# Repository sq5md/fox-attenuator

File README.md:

# Tłumik odbiorczy do łowów na lisa 
Przedmiotem opisu jest urządzenie do tłumienia sygnału pochodzącego z anteny w celu umożliwienia kierunkowego namierzania bliskich urządzeń nadawczych małej mocy takich jak np. nadajniki do łowów na lisa.

Projekt powstał jako potrzeba klubowa SP5YAM z Komorowa.

Autorzy:

Elektronika + oprogramowanie: **Marcin SQ5MD**

Obudowa: **Michał SP5LEL**

Konsultacje: **Klub SP5YAM**

## Zanim zbudujesz

Zanim zbudujesz, miej na uwadze że PCB v1 zawiera błędy i wymaga **cięcia ścieżek**, dolutowania 3 elementów oraz **poprowadzenia 2 cienkich kynarów do układu QFN**.

Projekt PCB v2 w toku.

## Opis głównych funkcji:

- 2 złącza SMA, jedno do podłączenia anteny, drugie do podłączenia odbiornika.
- Zasilanie z 1 ogniwa 18650
- Wbudowana ładowarka 500mA (USB C)
- Sygnalizacja naładowania na diodzie RGB
- Sygnalizacja tłumienia na diodzie RGB oraz na pasku 5xLED
- Interfejs użytkownika - enkoder kwadraturowy (12 imp na obrót) z przyciskiem
- Tłumienie teoretyczne 0-63dB z krokiem co 0,5dB
- Bypass antenowy 50Ω - do namierzania bez kierunku z bardzo bliskiej odległości
- Tłumienie zmierzone: 2.2-64.2dB (bypass do 80dB)
- Auto Power Off po określonym czasie nieaktywności
- Dioda RGB

## Obsługa

Urządzenie po włączeniu jest od razu gotowe do pracy sygnalizując to zaświeceniem diody LED na zielono.
Kręcenie enkoderem powoduje odpowiednio zwiększenie lub zmniejszenie tłumienia z krokiem 0.5dB. 

Stan tłumienia sygnalizowany jest diodą RGB:
- Intensywny zielony - brak tłumienia
- Zielony-poprzez żółty, pomarańczowy, czerwony - aktywne tłumienie w zależności od koloru LED
- Intensywny czerwony - tłumienie maksymalne
- Niebieski - stan odcięcia anteny. Bypass Z=50Ω.

Urządzenie włączamy i wyłączamy przyciskiem na enkoderze.

Urządzenie posiada wbudowaną ładowarkę (MCP73831), a stan naładowania sygnalizowany jest kolorem fioletowym.

Projekt można przetestować na stoisku SP5YAM w Burzeninie 2026 podczas zabawy w łowy na lisa. Dostępne są 2 sztuki.

## Konstrukcja

Tor antenowy układu składa się z poszczególnych elementów (kolejność od strony podłączania odbiornika):
- Złącze SMA (żeńskie)
- RF-Switch AS179 (rozdziela tor odbiorczy na tor antenowy i bypass Z=50Ω)
	- Do anteny: 2 x cyfrowy tłumik regulowany Berex BDA4601 sterowany z mikrokontrolera
	- Bypass: Rezystancja Z=50Ω, pomija oba tłumiki.

 Układ sterowany jest z mikrokontrolera RP2040 (płyta RP2040-Zero od Waveshare https://www.waveshare.com/wiki/RP2040-Zero )

Interfejs użytkownika stanowi enkoder kwadraturowy z przyciskiem, 5 diod LED, dioda LED RGB.

Urządzenie jest zasilane z jednego ogniwa Li-Ion 18650, oraz posiada wbudowaną ładowarkę MCP73831.

Elementy Q1 i D5 pozwalają zrealizować funkcję programowego wyłączenia urządzenia..

### Schemat

### PCB

Płytka drukowana wykonana została w technologii 2 warstwowej na laminacie FR4 o grubości 0.6mm aby zapewnić najlepsze dopasowanie do impedancji 50Ω.

### Oprogramowanie

#### Moduły

Oprogramowanie układu oparte jest o projekt Zephyr, co przyspieszyło stworzenie projektu. Modułowa konstrukcja oprogramowania pozawala utrzymać porządek i lepiej zrozumieć budowę układu. W układzie można wydzielić kilka głównych modułów które komunikują się ze sobą za pomocą wiadomości wysyłanych przez magistralę EventBus.  
Magistrala EventBus pozwala każdemu z modułów na subskrypcję poszczególnych rodzajów eventów (model Publish/Subscribe).

##### Moduł InputListener

Moduł odpowiada za odpowiedni odczyt eventów z systemu Zephyr i ich wysłanie na magistralę eventów EventBus.
Eventy które wysyła to:
- EncoderRotated(lewo/prawo) - (gdy wykryto przekręcenie enkodera w lewo lub prawo)
- EncoderPressEvent(wciśnięcie/puszczenie) - gdy wyrkryto wciśnięcie lub puszczenie przycisku
- ChargerEvent - gdy wykryto stan naładowania z ładowarki
##### Moduł logiki aplikacji

Obsługuje wiadomości:
- EncoderRotated - wysłanie eventu AttenuatorChange
- EncoderPressEvent - wysłanie eventu PowerOff
- ChargerEvent - wysłanie eventu RgbLedSet()
- AttenuationInfo - wysłanie eventu RgbLedSet oraz LedMatrixSet w zależności od wartości tłumienia

##### Moduł HW
Obsługuje wiadomości:
- LedMatrixSet - ustawienie stanu na diodach 5xLED
- PowerOff - wyłączenie układu
- RgbLedSet - ustawienie odpowiedniego koloru na diodzie RGB
- ApplyAttenuatorChange - zmiana tłumienia (lub bypass)

#### Bootloader
Mikrokontroler posiada wbudowany bootloader.
Aktualizacja oprogramowania jest możliwa za pomocą przewodu USB-C.
Jest to standardowy bootloader wbudowany w mikrokontroler RP2040.

### Obudowa

Do układu powstała obudowa wykonana w technologii druku 3D FDM, autorem obudowy jest Michał SP5LEL.
Na moment pisania tej treści nie ma dostępnych fotografii obudowy.

### Fotografie

## Pomiary

Urządzenie pomiarowe:
NanoVNA V2 od NanoRFE (https://nanorfe.com/pl/)
Aplikacja:
VNA_View na Linux

Parametry pomiarowe:
Sweep 144-440MHz, 1024 punkty, AVG=5
kalibracja SOLT

### Minimalne tłumienie

### Połowa skali

### Maksymalne tłumienie

### Bypass

Tor bypassu jest najbardziej wrażliwy na ekranowanie urządzenia.

## TODO:

- [ ] Poprawki PCB: brak sygnału LE, brak DC-blockerów RF
- [ ] Diody LED THT zamiast SMD
- [ ] Tylko jeden tłumik regulowany, drugi stały 30dB
- [ ] Wymiana ładowarki jest bardzo trudna - montować układ inaczej
- [ ] Integracja z odbiornikiem (żeby nie trzeba było podłączać zewnętrznego odbiornika)
- [ ] Dodać pomiar napięcia baterii
- [ ] Wrzucić do releases plik uf2

## Przeróbka PCB v1 aby działała

## Edytor schematów i pcb

Stworzone w Kicad 10.0.4

## Jak skompilować

1. Zainstaluj Zephyra: https://docs.zephyrproject.org/latest/develop/getting_started/index.html
2. Zainstaluj i skonfiguruj CLion: https://docs.zephyrproject.org/latest/develop/tools/clion.html
3. Otwórz projekt in CLion, otwórz folder w którym znajduje się główny plik CMakeLists.txt (w momencie pisania tej treści jest to folder 'software/fox-attenuator')
4. Uruchom płytkę RP2040-Zero w trybie bootloadera a następnie wybierz target "flash" w CLion i uruchom budowanie projektu.

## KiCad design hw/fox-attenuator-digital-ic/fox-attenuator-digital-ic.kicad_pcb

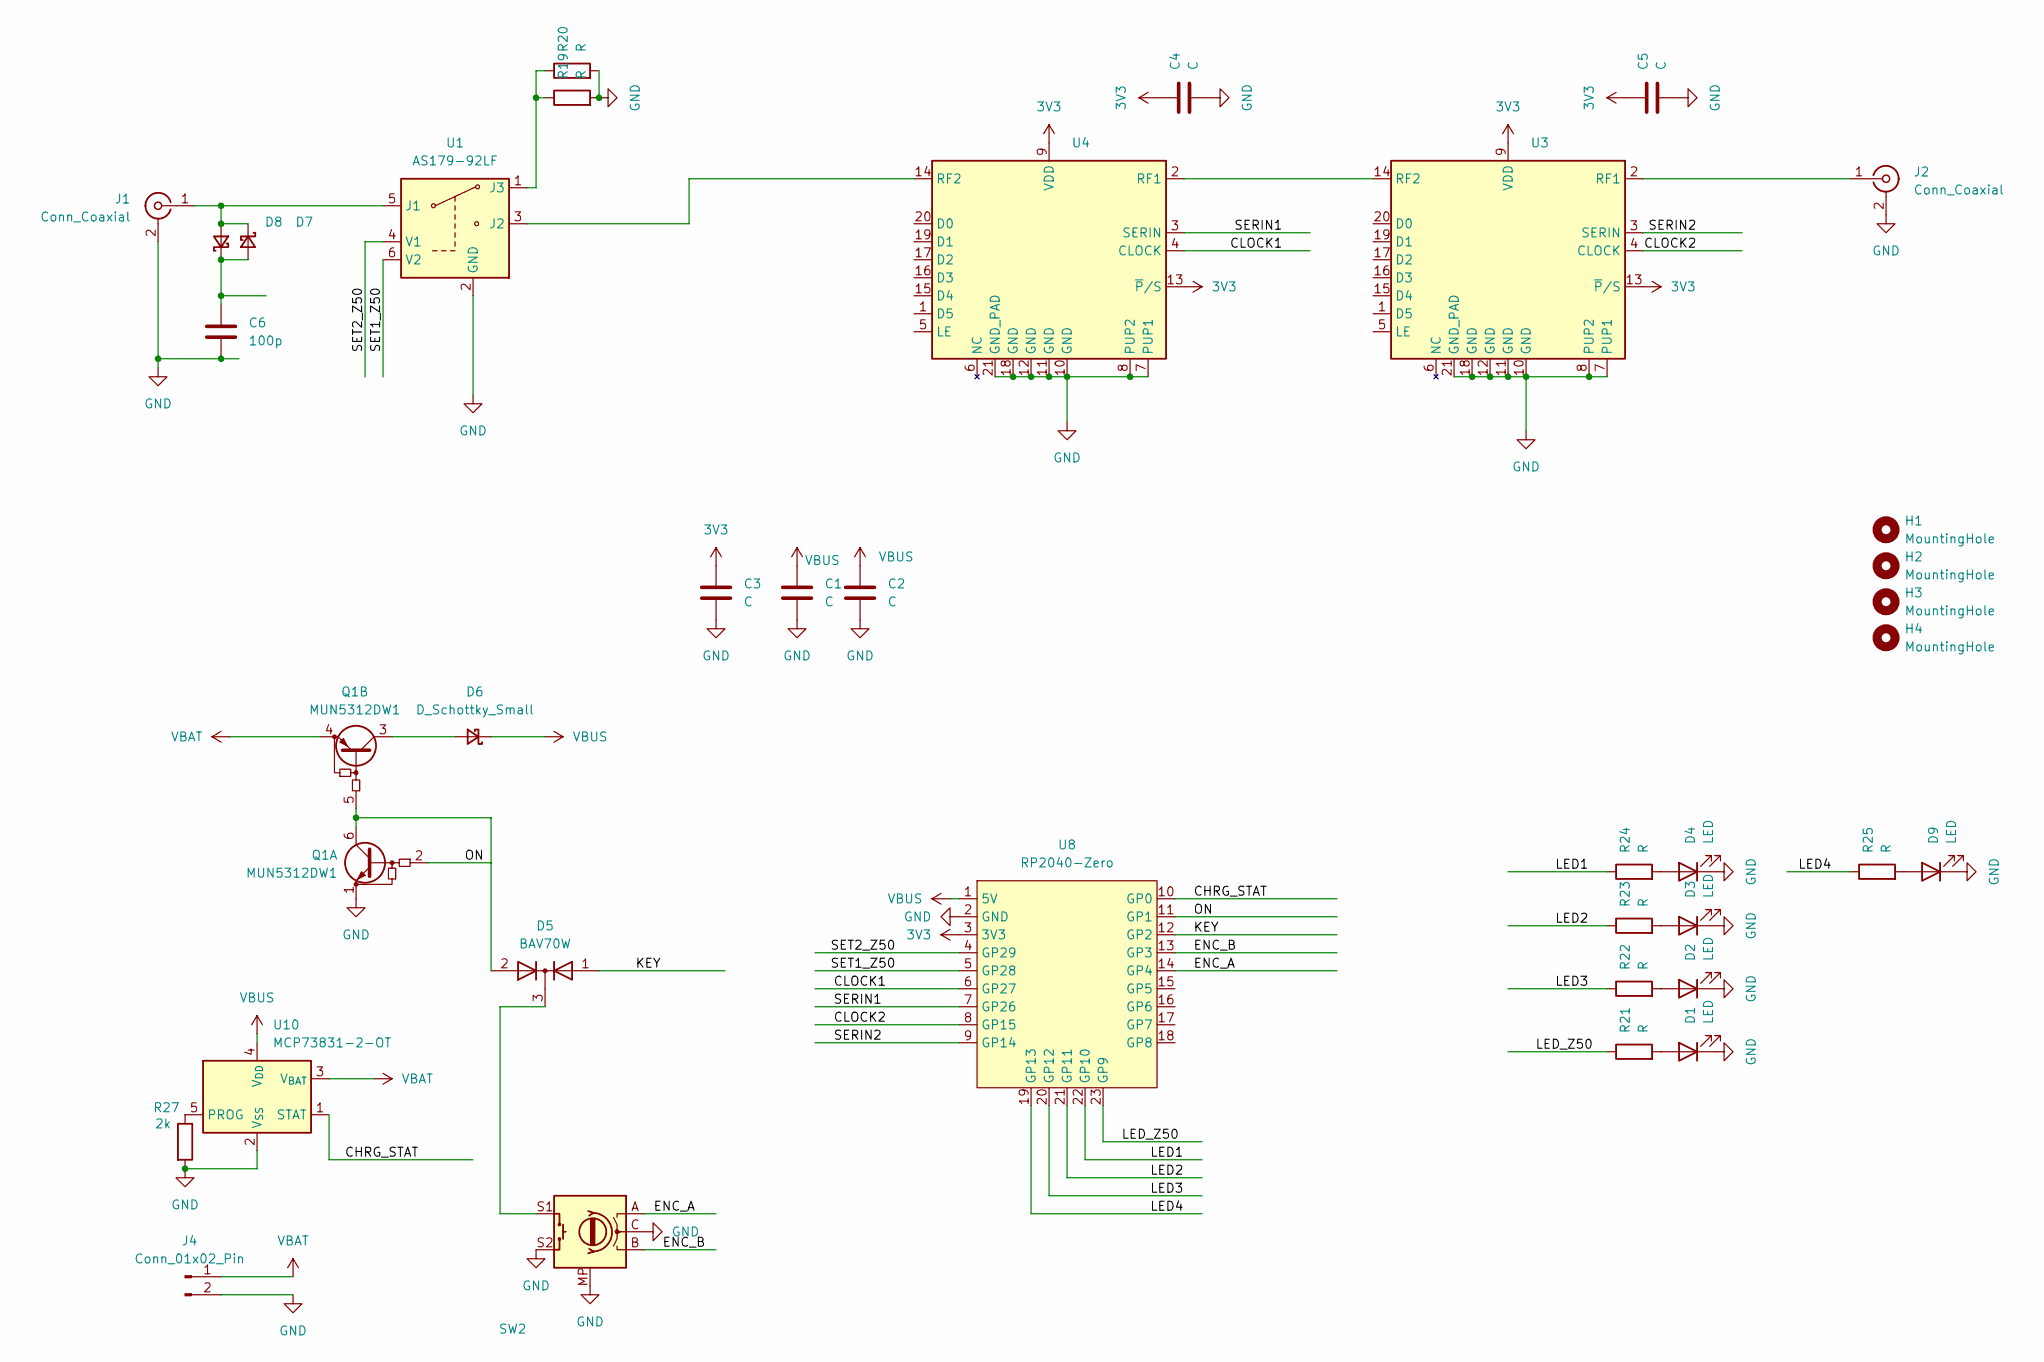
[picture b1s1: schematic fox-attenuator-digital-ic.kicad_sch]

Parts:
C1, C2, C3, C4, C5: C; C_0805_2012Metric_Pad1.18x1.45mm_HandSolder
C6: 100p; C_0805_2012Metric_Pad1.18x1.45mm_HandSolder
D1, D2, D3, D4, D9: LED; LED_0603_1608Metric_Pad1.05x0.95mm_HandSolder
D5: BAV70W; SOT-323_SC-70
D6, D7, D8: D_Schottky_Small; D_0603_1608Metric
H1, H2, H3, H4: MountingHole; MountingHole_3.2mm_M3_Pad_TopBottom
J1, J2: Conn_Coaxial; SMA_Molex_73251-1153_EdgeMount_Horizontal
J4: Conn_01x02_Pin; JST_PH_B2B-PH-K_1x02_P2.00mm_Vertical
Q1: MUN5312DW1; SOT-363_SC-70-6
R19, R20, R21, R22, R23, R24, R25: R; R_0603_1608Metric_Pad0.98x0.95mm_HandSolder
R27: 2k; R_0603_1608Metric
SW2: RotaryEncoder_Switch_MP; RotaryEncoder_Alps_EC11E-Switch_Vertical_H20mm
U1: AS179-92LF; SOT-363_SC-70-6
U3, U4: TQFN-20-1EP_4x4mm_P0.5mm_EP2.1x2.1mm
U8: RP2040-Zero; RP2040 Zero
U10: MCP73831-2-OT; SOT-23-5

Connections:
3V3: C3.1, C4.1, C5.1, U3.9 (VDD), U3.13 (~P/S), U4.9 (VDD), U4.13 (~P/S), U8.3 (3V3)
/CHRG_STAT: U8.10 (GP0), U10.1 (STAT)
/CLOCK1: U4.4 (CLOCK), U8.6 (GP27)
/CLOCK2: U3.4 (CLOCK), U8.8 (GP15)
/ENC_A: SW2.A, U8.14 (GP4)
/ENC_B: SW2.B, U8.13 (GP3)
/KEY: D5.1 (A), U8.12 (GP2)
/LED1: R24.1, U8.22 (GP10)
/LED2: R23.1, U8.21 (GP11)
/LED3: R22.1, U8.20 (GP12)
/LED4: R25.1, U8.19 (GP13)
/LED_Z50: R21.1, U8.23 (GP9)
/ON: Q1.2 (B1), U8.11 (GP1)
/SERIN1: U4.3 (SERIN), U8.7 (GP26)
/SERIN2: U3.3 (SERIN), U8.9 (GP14)
/SET1_Z50: U1.6 (V2), U8.5 (GP28)
/SET2_Z50: U1.4 (V1), U8.4 (GP29)
GND: C1.2, C2.2, C3.2, C4.2, C5.2, C6.2, D1.1 (K), D2.1 (K), D3.1 (K), D4.1 (K), D9.1 (K), H3.1, J1.2 (Ext), J2.2 (Ext), J4.2, Q1.1 (E1), R19.2, R20.2, R27.2, SW2.C, SW2.MP, SW2.S2, U1.2 (GND), U3.7 (PUP1), U3.8 (PUP2), U3.10 (GND), U3.11 (GND), U3.12 (GND), U3.18 (GND), U3.21 (GND_PAD), U4.7 (PUP1), U4.8 (PUP2), U4.10 (GND), U4.11 (GND), U4.12 (GND), U4.18 (GND), U4.21 (GND_PAD), U8.2 (GND), U10.2 (V_{SS})
unnamed: D1.2 (A), R21.2
unnamed: D2.2 (A), R22.2
unnamed: D3.2 (A), R23.2
unnamed: D4.2 (A), R24.2
unnamed: D5.3 (K), SW2.S1
unnamed: D6.2 (A), Q1.3 (C2)
unnamed: C6.1, D7.2 (A), D8.1 (K)
unnamed: D7.1 (K), D8.2 (A), J1.1 (In), U1.5 (J1)
unnamed: D9.2 (A), R25.2
unnamed: J2.1 (In), U3.2 (RF1)
unnamed: D5.2 (A), Q1.5 (B2), Q1.6 (C1)
unnamed: U1.3 (J2), U4.14 (RF2)
unnamed: R19.1, R20.1, U1.1 (J3)
unnamed: U3.14 (RF2), U4.2 (RF1)
unnamed: R27.1, U10.5 (PROG)
VBAT: J4.1, Q1.4 (E2), U10.3 (V_{BAT})
VBUS: C1.1, C2.1, D6.1 (K), U8.1 (5V), U10.4 (V_{DD})

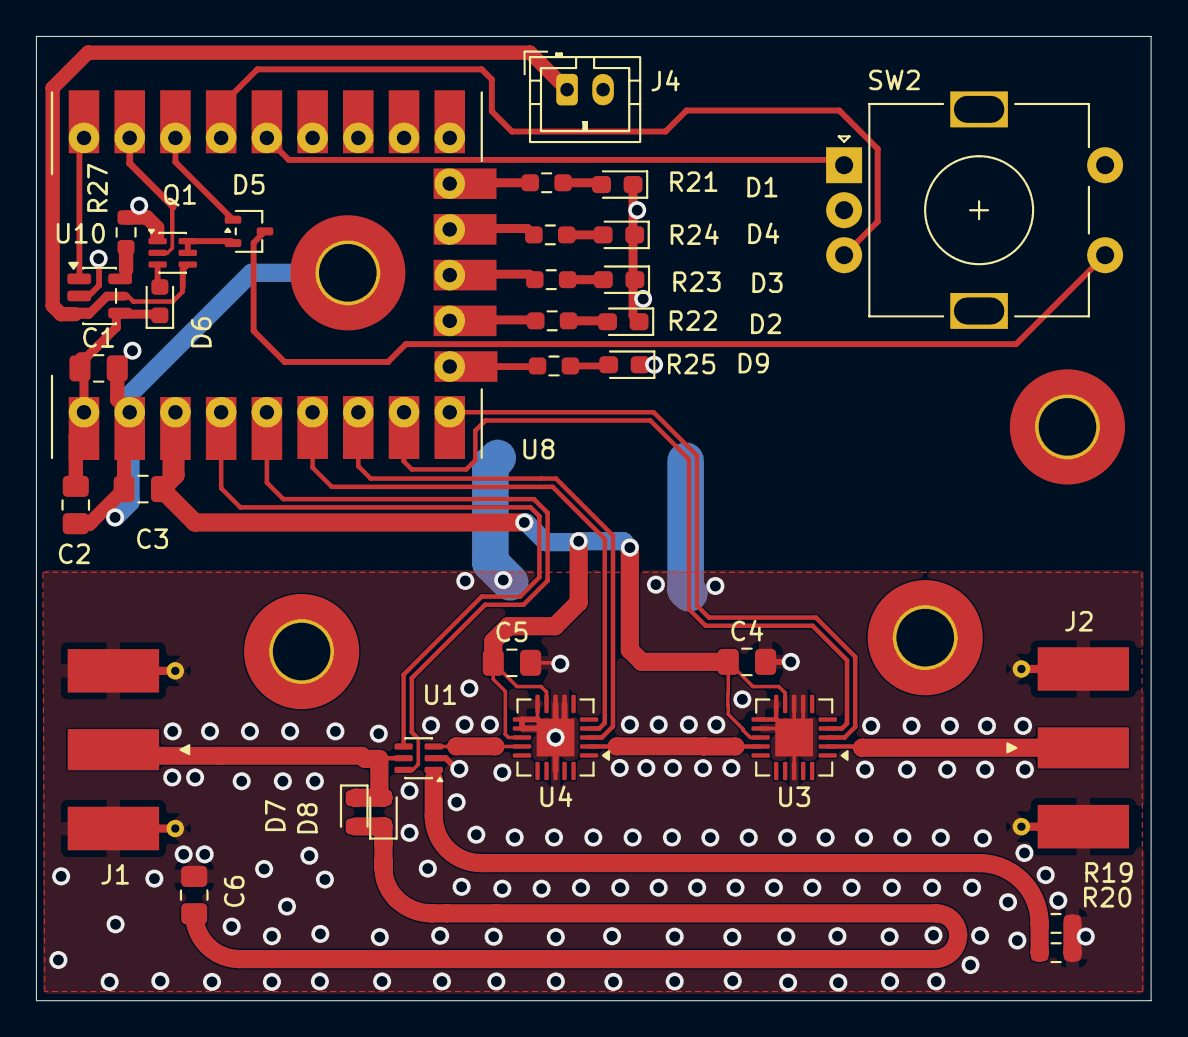
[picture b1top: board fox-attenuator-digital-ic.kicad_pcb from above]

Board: 2 copper layers, 61.9 x 53.6 mm, 37 parts (0 on the bottom side), 35 nets.

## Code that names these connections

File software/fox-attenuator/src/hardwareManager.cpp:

#include "hardwareManager.hpp"

#include "event.hpp"

#include <algorithm>
#include <optional>
#include <zephyr/drivers/gpio.h>
#include <zephyr/usb/usbd.h>

namespace
{
    K_THREAD_STACK_DEFINE(hardwareManagerStack, 2048);
    const gpio_dt_spec led0    = GPIO_DT_SPEC_GET(DT_NODELABEL(led9), gpios);
    const gpio_dt_spec led1    = GPIO_DT_SPEC_GET(DT_NODELABEL(led10), gpios);
    const gpio_dt_spec led2    = GPIO_DT_SPEC_GET(DT_NODELABEL(led11), gpios);
    const gpio_dt_spec led3    = GPIO_DT_SPEC_GET(DT_NODELABEL(led12), gpios);
    const gpio_dt_spec led4    = GPIO_DT_SPEC_GET(DT_NODELABEL(led13), gpios);
    const gpio_dt_spec pwrOff  = GPIO_DT_SPEC_GET(DT_NODELABEL(pwr_off_gpio), gpios);
    const gpio_dt_spec btnGpio = GPIO_DT_SPEC_GET(DT_NODELABEL(btn_gpio), gpios);
    const gpio_dt_spec clk1    = GPIO_DT_SPEC_GET(DT_ALIAS(bda_clk1), gpios);
    const gpio_dt_spec serin1  = GPIO_DT_SPEC_GET(DT_ALIAS(bda_serin1), gpios);
    const gpio_dt_spec clk2    = GPIO_DT_SPEC_GET(DT_ALIAS(bda_clk2), gpios);
    const gpio_dt_spec serin2  = GPIO_DT_SPEC_GET(DT_ALIAS(bda_serin2), gpios);
    const gpio_dt_spec le      = GPIO_DT_SPEC_GET(DT_ALIAS(bda_le), gpios);
    const gpio_dt_spec rfCtrl  = GPIO_DT_SPEC_GET(DT_ALIAS(rf_sw_ctrl), gpios);
    const gpio_dt_spec rfCtrlN = GPIO_DT_SPEC_GET(DT_ALIAS(rf_sw_ctrl_n), gpios);
    const device* ledStrip     = DEVICE_DT_GET(DT_ALIAS(led_strip));

    USBD_DEVICE_DEFINE(usbdevice, DEVICE_DT_GET(DT_NODELABEL(zephyr_udc0)), 0x2e8a, 0x000a);

    USBD_DESC_LANG_DEFINE(usbdlang);
    USBD_DESC_MANUFACTURER_DEFINE(usbdeviceManufacturer, "SP5YAM");
    USBD_DESC_PRODUCT_DEFINE(usbdeviceProduct, "Fox attenuator");

    // 500 mA declararion
    USBD_CONFIGURATION_DEFINE(usbdeviceConfig, USB_SCD_SELF_POWERED, 250, nullptr);

} // namespace

namespace
{
    std::optional<HardwareManager> hardwareManagerObj;
}

HardwareManager* HardwareManager::Create(msgbus::Bus& bus)
{
    if (not hardwareManagerObj) {
        hardwareManagerObj.emplace(Key{}, bus);
        if (hardwareManagerObj->initialized_) {
            return &hardwareManagerObj.value();
        }
        hardwareManagerObj = std::nullopt;
    }
    return nullptr;
}

bool isBitSet(uint8_t val, uint8_t bit)
{
    return (val & (1 << bit)) != 0;
}

void HardwareManager::Handle(const msgbus::events::LedMatrixSet& lm) noexcept
{
    const auto val = lm.value;
    gpio_pin_set_dt(&led0, isBitSet(val, 0) ? 1 : 0);
    gpio_pin_set_dt(&led1, isBitSet(val, 1) ? 1 : 0);
    gpio_pin_set_dt(&led2, isBitSet(val, 2) ? 1 : 0);
    gpio_pin_set_dt(&led3, isBitSet(val, 3) ? 1 : 0);
    gpio_pin_set_dt(&led4, isBitSet(val, 4) ? 1 : 0);
}
void HardwareManager::Handle(const msgbus::events::PowerOff& ph) noexcept
{
    SetPinPowerOff();
}
void HardwareManager::Handle(const msgbus::events::RgbLedSet& rgb) noexcept
{
    rgbLed_.SetColor(rgb.color);
}
void HardwareManager::Handle(const msgbus::events::ApplyAttenuationChange& aac) noexcept
{
    attenuator_.Apply(aac.value);
    const auto attenuator0Val = attenuator_.GetAttenuatorBits(0);
    const auto attenuator1Val = attenuator_.GetAttenuatorBits(1);
    SetAttenuator(attenuator0Val, attenuator1Val);

    if (attenuator_.GetBypass()) {
        RfSwitchSetPath(true);
    }
    else {
        RfSwitchSetPath(false);
    }

    msgBus_.Publish(msgbus::events::AttenuationInfo{.attenuationHalfDb    = attenuator_.GetAttenuation(),
                                                    .maxAttenuationHalfDb = Attenuator::GetMaxAttenuation(),
                                                    .bypass               = attenuator_.GetBypass()});
}
void HardwareManager::EnqueueEvent(const EventVariant& event) noexcept
{
    k_msgq_put(&msgQueue_, &event, K_NO_WAIT);
}

HardwareManager::HardwareManager(Key, msgbus::Bus& bus)
    : subLedMatrixSet_{*this}, subPowerHoldSet_{*this}, subRgbLedSet_{*this}, subApplyAttenuationChange_{*this},
      msgBus_(bus), rgbLed_(ledStrip)
{
    initialized_ = SetupHardware();
    if (not initialized_) {
        return;
    }

    bus.Subscribe(subLedMatrixSet_);
    bus.Subscribe(subPowerHoldSet_);
    bus.Subscribe(subRgbLedSet_);
    bus.Subscribe(subApplyAttenuationChange_);

    k_msgq_init(&msgQueue_, msgBuffer_.data(), sizeof(EventVariant), kQueueDepth);
    k_thread_create(&threadData_,
                    hardwareManagerStack,
                    K_THREAD_STACK_SIZEOF(hardwareManagerStack),
                    ThreadEntry,
                    this,
                    nullptr,
                    nullptr,
                    K_PRIO_COOP(7),
                    0,
                    K_NO_WAIT);
}

// helpers
namespace
{
    template <std::size_t N> bool IsReady(const std::array<const gpio_dt_spec*, N>& ary)
    {
        return std::ranges::all_of(
            ary.begin(), ary.end(), [](const gpio_dt_spec* item) { return gpio_is_ready_dt(item); });
    }

    template <std::size_t N> void SetInactive(const std::array<const gpio_dt_spec*, N>& ary)
    {
        std::ranges::for_each(ary.begin(), ary.end(), [](const gpio_dt_spec* item) {
            gpio_pin_configure_dt(item, GPIO_OUTPUT_INACTIVE);
        });
    }

    template <std::size_t N> void SetInput(const std::array<const gpio_dt_spec*, N>& ary)
    {
        std::ranges::for_each(
            ary.begin(), ary.end(), [](const gpio_dt_spec* item) { gpio_pin_configure_dt(item, GPIO_INPUT); });
    }
} // namespace

bool HardwareManager::SetupHardware() noexcept
{
    const std::array outputs = std::to_array(
        {&pwrOff, &led0, &led1, &led2, &led3, &led4, &le, &clk1, &clk2, &serin1, &serin2, &rfCtrl, &rfCtrlN});
    const std::array inputs = std::to_array({&btnGpio});

    if (not IsReady(inputs)) {
        return false;
    }
    if (not IsReady(outputs)) {
        return false;
    }
    SetInactive(outputs);
    SetInput(inputs);

    if (SetupUsb() < 0) {
        return false;
    }

    if (not rgbLed_.Ready()) {
        return false;
    }

    return true;
}

int HardwareManager::SetupUsb()
{
    const device* kUsbSerialPort0 = DEVICE_DT_GET(DT_NODELABEL(cdc_acm_uart0));
    if (!device_is_ready(kUsbSerialPort0)) {
        return -ENODEV;
    }
    const device* kUsbSerialPort1 = DEVICE_DT_GET(DT_NODELABEL(cdc_acm_uart1));
    if (!device_is_ready(kUsbSerialPort1)) {
        return -ENODEV;
    }

    int err;

    err = usbd_add_descriptor(&usbdevice, &usbdlang);
    if (err) {
        return err;
    }

    err = usbd_add_descriptor(&usbdevice, &usbdeviceManufacturer);
    if (err) {
        return err;
    }

    err = usbd_add_descriptor(&usbdevice, &usbdeviceProduct);
    if (err) {
        return err;
    }

    err = usbd_add_configuration(&usbdevice, USBD_SPEED_FS, &usbdeviceConfig);
    if (err) {
        return err;
    }

    err = usbd_register_all_classes(&usbdevice, USBD_SPEED_FS, 1, nullptr);
    if (err) {
        return err;
    }

    err = usbd_init(&usbdevice);
    if (err) {
        return err;
    }

    return usbd_enable(&usbdevice);
}

void HardwareManager::ProcessEvent(const msgbus::SystemEvents::EventVariant& event) noexcept
{
    std::visit(
        [this](const auto& concrete_event) {
            if constexpr (requires { Handle(concrete_event); }) {
                Handle(concrete_event);
            }
        },
        event);
}

void HardwareManager::Run()
{
    msgbus::SystemEvents::EventVariant event;
    while (true) {
        if (k_msgq_get(&msgQueue_, &event, K_FOREVER) == 0) {
            ProcessEvent(event);
        }
    }
}
void HardwareManager::RfSwitchSetPath(bool antennaBypass)
{
    gpio_pin_set_dt(&rfCtrl, antennaBypass ? 0 : 1);
    gpio_pin_set_dt(&rfCtrlN, antennaBypass ? 0 : 1);
}

void HardwareManager::SetAttenuator(uint8_t value1, uint8_t value2)
{
    gpio_pin_set_dt(&clk1, 0);
    gpio_pin_set_dt(&serin1, 0);
    gpio_pin_set_dt(&clk2, 0);
    gpio_pin_set_dt(&serin2, 0);

    for (unsigned i = 0; i < 6; i++) {
        const auto shift       = i;
        const auto val1Shifted = (value1 & (0b100000U >> shift)) != 0;
        const auto val2Shifted = (value2 & (0b100000U >> shift)) != 0;
        gpio_pin_set_dt(&serin1, val1Shifted);
        gpio_pin_set_dt(&serin2, val2Shifted);
        k_busy_wait(1);
        gpio_pin_set_dt(&clk1, 1);
        gpio_pin_set_dt(&clk2, 1);
        k_busy_wait(1);
        gpio_pin_set_dt(&clk1, 0);
        gpio_pin_set_dt(&clk2, 0);
        k_busy_wait(1);
        gpio_pin_set_dt(&serin1, 0);
        gpio_pin_set_dt(&serin2, 0);
        k_busy_wait(10);
    }

    k_busy_wait(6);
    gpio_pin_set_dt(&le, 1);
    k_busy_wait(6);
    gpio_pin_set_dt(&le, 0);
}

void HardwareManager::SetPinPowerOff()
{
    gpio_pin_set_dt(&pwrOff, 1);
}

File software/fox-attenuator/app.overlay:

#include <zephyr/dt-bindings/input/input-event-codes.h>

/ {
	chosen {
		zephyr,console = &cdc_acm_uart0;
		zephyr,shell-uart = &cdc_acm_uart1;
	};

	aliases {
		led-ws2812 = &led_strip;
		chg-status = &chg_stat_gpio;
		pwr-off = &pwr_off_gpio;
		btn0 = &btn_gpio;
		encoder0 = &encoder;

		bda-clk1 = &bda_clk1;
		bda-serin1 = &bda_serin1;
		bda-clk2 = &bda_clk2;
		bda-serin2 = &bda_serin2;
		bda-le = &bda_le;

		rf-sw-ctrl = &rf_sw_ctrl;
		rf-sw-ctrl-n = &rf_sw_ctrl_n;

	};

	leds {
		compatible = "gpio-leds";

		led9: led_9 {
			gpios = <&gpio0 9 GPIO_ACTIVE_HIGH>;
			label = "LED GP9";
		};

		led10: led_10 {
			gpios = <&gpio0 10 GPIO_ACTIVE_HIGH>;
			label = "LED GP10";
		};

		led11: led_11 {
			gpios = <&gpio0 11 GPIO_ACTIVE_HIGH>;
			label = "LED GP11";
		};

		led12: led_12 {
			gpios = <&gpio0 12 GPIO_ACTIVE_HIGH>;
			label = "LED GP12";
		};

		led13: led_13 {
			gpios = <&gpio0 13 GPIO_ACTIVE_HIGH>;
			label = "LED GP13";
		};
	};

	rf_switch {
		compatible = "gpio-leds";

		rf_sw_ctrl: rf_sw_ctrl {
			gpios = <&gpio0 28 GPIO_ACTIVE_HIGH>;
			label = "RF Switch CTRL (GP28)";
		};

		rf_sw_ctrl_n: rf_sw_ctrl_n {
			gpios = <&gpio0 29 GPIO_ACTIVE_LOW>;
			label = "RF Switch CTRL Inverse (GP29)";
		};
	};

	gpio_keys {
		compatible = "gpio-keys";

		chg_stat_gpio: chg_stat {
			gpios = <&gpio0 0 (GPIO_PULL_UP | GPIO_ACTIVE_LOW)>;
			label = "Charging Status";
			zephyr,code = <INPUT_KEY_0>;
		};

		btn_gpio: button_2 {
			gpios = <&gpio0 2 (GPIO_PULL_UP | GPIO_ACTIVE_LOW)>;
			label = "Encoder button";
			zephyr,code = <INPUT_KEY_ENTER>;
		};
	};

	pwr_ctrl {
		compatible = "gpio-leds";

		pwr_off_gpio: pwr_off {
			gpios = <&gpio0 1 GPIO_ACTIVE_LOW>;
			label = "Power Hold";
		};
	};

	bda4601_if {
		compatible = "gpio-leds";

		bda_clk1: bda_clk1 {
			gpios = <&gpio0 27 GPIO_ACTIVE_HIGH>;
			label = "BDA4601 CLOCK1 (GP27)";
		};

		bda_serin1: bda_serin1 {
			gpios = <&gpio0 26 GPIO_ACTIVE_HIGH>;
			label = "BDA4601 SERIN1 (GP26)";
		};

		bda_clk2: bda_clk2 {
			gpios = <&gpio0 15 GPIO_ACTIVE_HIGH>;
			label = "BDA4601 CLOCK2 (GP15)";
		};

		bda_serin2: bda_serin2 {
			gpios = <&gpio0 14 GPIO_ACTIVE_HIGH>;
			label = "BDA4601 SERIN2 (GP14)";
		};

		bda_le: bda_le {
			gpios = <&gpio0 8 (GPIO_ACTIVE_HIGH)>;
			label = "BDA4601 LE (GP8)";
		};
	};

	encoder: encoder {
		compatible = "gpio-qdec";
		gpios = <&gpio0 4 (GPIO_PULL_UP | GPIO_ACTIVE_HIGH)>, /* Phase A */
		        <&gpio0 3 (GPIO_PULL_UP | GPIO_ACTIVE_HIGH)>; /* Phase B */
		steps-per-period = <4>;
		sample-time-us = <200>;
		idle-timeout-ms = <100>;
		zephyr,axis = <0>;
		label = "Incremental Encoder";
	};

};

&uart0 {
	status = "disabled";
};

&zephyr_udc0 {
	cdc_acm_uart0: cdc_acm_uart0 {
		compatible = "zephyr,cdc-acm-uart";
	};

	cdc_acm_uart1: cdc_acm_uart1 {
		compatible = "zephyr,cdc-acm-uart";
	};
};

&pio0 {
	status = "okay";

	pio_ws2812: ws2812 {
		status = "okay";
		compatible = "worldsemi,ws2812-rpi-pio";
		bit-waveform = <3 3 4>;
		pinctrl-0 = <&ws2812_default>;
		pinctrl-names = "default";

		led_strip: led_strip {
			status = "okay";
			compatible = "worldsemi,ws2812-pb";
			chain-length = <1>;
			color-mapping = <LED_COLOR_ID_BLUE LED_COLOR_ID_RED LED_COLOR_ID_GREEN>;
			reset-delay = <64>;
		};
	};
};

&pinctrl {
	ws2812_default: ws2812_default {
		group1 {
			pinmux = <PIO0_P16>;
		};
	};
};

&clk_sys {
	clock-frequency = <DT_FREQ_M(48)>;
};

&clk_peri {
	clock-frequency = <DT_FREQ_M(48)>;
};

&vreg {
	raspberrypi,brown-out-detection;

	/* in uV
	 * Default: 860000 (0.86V).
	 * - 860000  (0.86V)
	 * - 903000  (0.903V)
	 * - 946000  (0.946V)
	 * - 989000  (0.989V)
	 * - 1032000 (1.032V)
	 */
	raspberrypi,brown-out-threshold = <1032000>;
};

&wdt0 {
	compatible = "raspberrypi,pico-watchdog";
	status = "okay";
};
